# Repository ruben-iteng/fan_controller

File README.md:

# fan_controller

## About
A simple controller for 4-pin PC fans with USB-PD as power input.
- 8x 4-pin PC fan connectors
- 2x 10kohm NTC temperature sensors connectors
- I2C via Qwiic connector
- USB-PD power input
    - 12V PD request voltage
    - PWR request ok LED
- EMC2101 fan controller
    - tachometer input (first fan connector)
    - PWM output (3.3V buffered fan PWM signal)
    - external temperature sensor
- 4x RGBW addressable LEDs
- ESP32C3 microcontroller

Created with [Atopile](https://atopile.com)

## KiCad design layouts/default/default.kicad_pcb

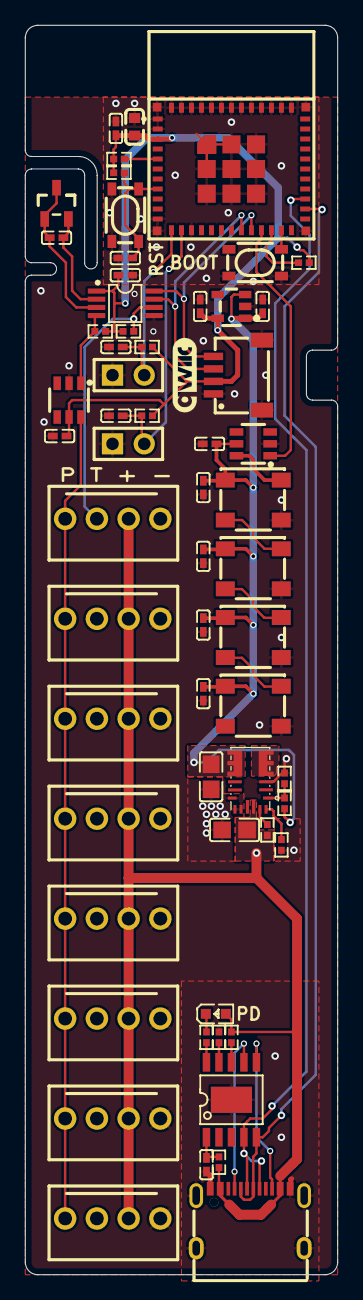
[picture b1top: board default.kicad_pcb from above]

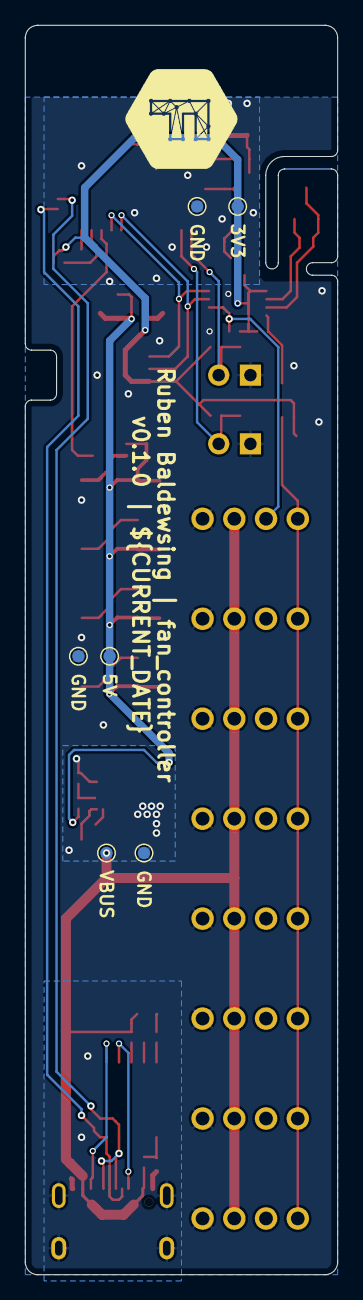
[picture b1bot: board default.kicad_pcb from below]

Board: 2 copper layers, 25.0 x 100.0 mm, 68 parts (7 on the bottom side), 34 nets.

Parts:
C1: 10µF ±10% 25V X5R; C0805-3b2e55
C2: 22µF ±10% 16V X5R; C0805-3b2e55
C3, C5, C6, C7, C8, C9, C10, C11, C12, C14, C17, C18: 100nF ±10% 16V X7R; C0402-b3ef17
C4: 2.2nF ±10% 50V X7R; C0402-b3ef17
C13: 22µF ±20% 6.3V X5R; C0603-bd72f6
C15, C16: 1µF ±10% 16V X5R; C0402-b3ef17
CN1, CN2, CN3, CN4, CN5, CN6, CN7, CN8: CONN-TH_4P-P2.54_HCTL_HC-2510-4A
CN9: CONN-SMD_4P-P1.00_SM04B-SRSS-TB-LF-SN-d36980
LED1, LED2, LED3, LED4: LED-SMD_4P-L5.0-W4.9-BR-4393b6
LOGO1: faebrykLogo_8x9mm
Q1: SOT-23-3_L2.9-W1.3-P1.90-LS2.4-TR-36f2d9
R1: 53.6kΩ ±1% 62.5mW; R0402-56259e
R2, R4: 100kΩ ±1% 62.5mW; R0402-56259e
R3: 19.1kΩ ±1% 62.5mW; R0402-56259e
R5, R6, R7, R8, R9, R10, R11, R14, R15: 10kΩ ±1% 62.5mW; R0402-56259e
R12: 1kΩ ±1% 62.5mW; R0402-56259e
R13: 24kΩ ±1% 62.5mW; R0402-56259e
TP1, TP2, TP3, TP4, TP5, TP6: TestPoint_Pad_D1.0mm
U1: QFN-20_L5.0-W3.0-TL-MPM3610GQV-Z-b63965
U2: MSOP-8_L3.0-W3.0-P0.65-LS4.9-BL-3bf91a
U3, U5: SOT-23-6_L2.9-W1.6-P0.95-LS2.8-BR-bfc73b
U4: LDO 3.3V ±0% 850.5mA 320mV Vin max Iq 10µA; SOT-23-5_L2.9-W1.6-P0.95-LS2.8-BR-2dcca4
U6, U8: KEY-SMD_4P-L4.2-W3.2-P2.20-LS4.6
U7: WIFIM-SMD_ESP32-C3-MINI-1-fcb454
U9: qwiic_6mm
U10: ESSOP-10_L4.9-W3.9-P1.0-LS6.0-TL-EP-20a8ca
U11: LED0603-RD
U12, U13: HDR-TH_2P-P2.54-V-F-f60f0d
USB1: USB-C-SMD_TYPE-C-6PIN-2MD-073-1d78f0

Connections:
ALERTh_TACH: CN8.2, R6.1, U2.6
EN_SYNC: R2.1, U1.17
FAN: R5.1, U2.4, U3.1
FB: R3.1, R4.2, U1.1
PG: R1.1, U1.18
base: C4.1, Q1.2, Q1.3, U2.3
cathode: R10.1, U11.1
emitter: C4.2, Q1.1, U2.2
gnd: C1.2, C2.2, C3.2, C5.2, C6.2, C7.2, C8.2, C9.2, C10.2, C11.2, C12.2, C13.2, C14.2, C15.2, C16.2, C17.2, C18.2, CN1.4, CN2.4, CN3.4, CN4.4, CN5.4, CN6.4, CN7.4, CN8.4, CN9.1, CN9.5, CN9.6, LED1.1, LED2.1, LED3.1, LED4.1, R1.2, R3.2, R13.2, TP1.1, TP3.1, TP5.1, U1.3, U1.12, U1.13, U1.14, U2.5, U3.2, U4.2, U5.2, U6.1, U6.2, U7.1, U7.2, U7.11, U7.14, U7.36, U7.37, U7.38, U7.39, U7.40, U7.41, U7.42, U7.43, U7.44, U7.45, U7.46, U7.47, U7.48, U7.49, U7.50, U7.51, U7.52, U7.53, U8.1, U8.2, U10.11, U12.1, U13.1, USB1.1, USB1.12, USB1.13, USB1.14
hv: C1.1, CN1.3, CN2.3, CN3.3, CN4.3, CN5.3, CN6.3, CN7.3, CN8.3, R2.2, R11.1, R12.1, TP6.1, U1.16, U11.2, USB1.2, USB1.11
hv-1: C3.1, C5.1, C7.1, C13.1, C14.1, CN9.2, R5.2, R6.2, R7.2, R8.2, R9.1, R14.2, R15.2, TP2.1, U2.1, U3.5, U4.5, U7.3
hv-2: C2.1, C6.1, C8.1, C9.1, C10.1, C11.1, C12.1, LED1.3, LED2.3, LED3.3, LED4.3, R4.1, TP4.1, U1.9, U4.1, U4.3, U5.5
line: CN9.3, U2.7, U7.19
line-1: C17.1, R14.1, U7.12, U12.2
line-3: U7.27, U10.4, USB1.6, USB1.8
line-4: LED2.4, LED3.2
line-5: LED1.4, LED2.2
line-6: R8.1, U7.22
line-7: C18.1, R15.1, U7.13, U13.2
line-8: R7.1, U7.5
line-10: CN1.1, CN2.1, CN3.1, CN4.1, CN5.1, CN6.1, CN7.1, CN8.1, U3.6
line-11: LED3.4, LED4.2
line-14: CN9.4, U2.8, U7.20
line-15: U5.1, U7.21
line-17: U7.26, U10.5, USB1.5, USB1.7
line-19: LED1.2, U5.6
output: U6.3, U6.4, U7.23
output-1: C15.1, R9.2, U7.8, U8.3, U8.4
usb_pd_power_sink-line: U10.6, USB1.10
usb_pd_power_sink-line-1: U10.7, USB1.4
usb_pd_power_sink.pd_trigger-gnd: R10.2, U10.10
usb_pd_power_sink.pd_trigger-hv: C16.1, R12.2, U10.1
usb_pd_power_sink.pd_trigger-line: R13.1, U10.9
usb_pd_power_sink.pd_trigger-line-1: R11.2, U10.8

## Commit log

2025-05-25 Update build workflow
2025-05-25 Initial design
2025-05-25 Fix dcdc converter connections
2025-05-25 Add missing fp-lib-table
2025-05-25 Check if manually edding it works
2025-05-29 Manually fix fp_lib table (#1)
